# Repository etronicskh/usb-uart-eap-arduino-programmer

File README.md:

# EPS and Arduino programmer
Open-source

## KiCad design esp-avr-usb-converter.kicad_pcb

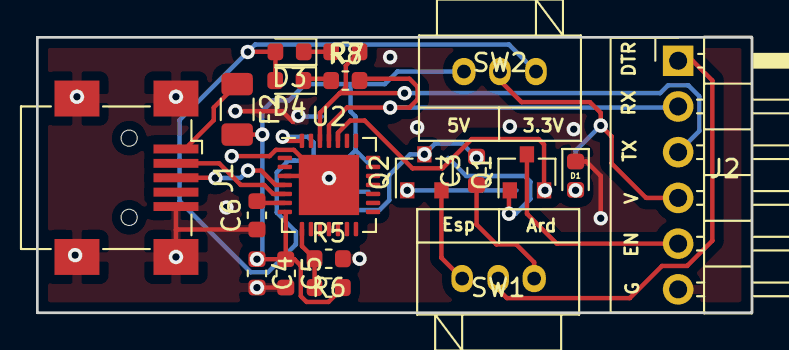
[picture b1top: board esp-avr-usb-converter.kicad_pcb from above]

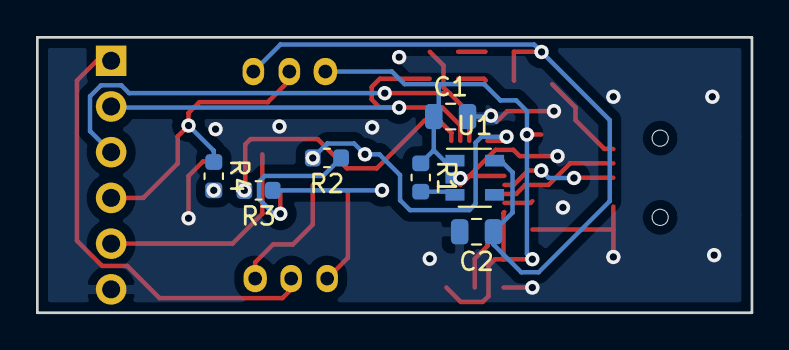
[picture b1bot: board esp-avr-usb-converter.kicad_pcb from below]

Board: 2 copper layers, 39.7 x 15.3 mm, 26 parts (7 on the bottom side), 23 nets.

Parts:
C1, C2: 10u; C_0805_2012Metric
C3, C4, C6: 100n; C_0603_1608Metric
C5: 1u; C_0603_1608Metric
D1: R; LED_0603_1608Metric
D3, D4: B; LED_0603_1608Metric
F2: 500mA; Fuse_1206_3216Metric
J1: USB_B_Mini; USB_Mini-B_Wuerth_65100516121_Horizontal
J2: con; PinHeader_1x06_P2.54mm_Horizontal
Q1, Q2: BSS138; SOT-23
R1, R2, R3: 10k; R_0603_1608Metric
R4, R7, R8: 1k; R_0603_1608Metric
R5: 47.5k; R_0603_1608Metric
R6: 22.1k; R_0603_1608Metric
SW1: Mode; SW-3P-SK12D07VG
SW2: 3.3V/5V; SW-3P-SK12D07VG
U1: SPX3819M5-L-3-3; SOT-23-5
U2: CP2102N-A01-GQFN28; QFN-28-1EP_5x5mm_P0.5mm_EP3.35x3.35mm

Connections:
+3V3: C2.1, D3.2, D4.2, SW2.1, U1.5
+5V: C1.1, C4.1, C5.1, F2.2, R1.1, R6.1, SW2.3, U1.1, U2.7
/CP2102N-GQFN28/D+: J1.3, U2.4
/CP2102N-GQFN28/D-: J1.2, U2.5
/CP2102N-GQFN28/VBUS: F2.1, J1.1
/CP2102N-GQFN28/VDD: C6.2, U2.6
/DTR: C3.2, Q2.3, R2.2, U2.28
/DTR_O: J2.1, SW1.2
/EN: J2.5, Q1.3
/ESP: Q2.2, SW1.1
/RTS: Q1.2, R3.2
/RX: J2.2, R8.2, U2.25
/TX: J2.3, R7.2, U2.26
GND: C1.2, C2.2, C4.2, C5.2, C6.1, D1.1, J1.5, J1.6, J2.6, R5.2, U1.2, U2.3, U2.29
unnamed: C3.1, SW1.3
unnamed: D1.2, R4.2
unnamed: D3.1, R7.1
unnamed: D4.1, R8.1
unnamed: Q1.1, R2.1
unnamed: Q2.1, R3.1
unnamed: R1.2, U1.3
unnamed: R5.1, R6.2, U2.8
VCC: J2.4, R4.1, SW2.2

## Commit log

2021-05-23 Add files
    - Fabrications
    - Tested
    - Wors
